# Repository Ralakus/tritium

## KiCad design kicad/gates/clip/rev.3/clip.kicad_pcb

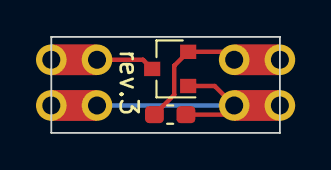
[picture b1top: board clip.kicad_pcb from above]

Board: 2 copper layers, 12.7 x 5.3 mm, 6 parts (0 on the bottom side), 3 nets.

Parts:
J1, J2, J3, J4: Conn_01x01; Hybrid_Castellation_1x01_P2.54
Q1: BSS84; SOT-23
R1: 470k; R_0603_1608Metric_Pad1.05x0.95mm_HandSolder

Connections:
Anode: J1.1, Q1.3
Cathode: J3.1, Q1.2, R1.1
GND: J2.1, J4.1, Q1.1, R1.2

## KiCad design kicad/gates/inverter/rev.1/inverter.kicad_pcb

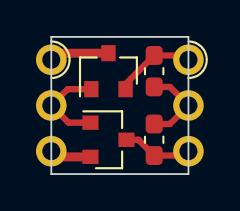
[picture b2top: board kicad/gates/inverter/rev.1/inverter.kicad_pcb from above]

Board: 2 copper layers, 7.6 x 7.6 mm, 6 parts (0 on the bottom side), 6 nets.

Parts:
J1, J2: Conn_01x03; Edge_Castellation_1x03_P2.54
Q1: BSS84; SOT-23
Q2: 2N7002; SOT-23
R1, R2: 12k; R_0603_1608Metric_Pad1.05x0.95mm_HandSolder

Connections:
In: J1.2, Q1.1, Q2.1
Nti: J2.3, Q2.3, R2.2
Out: J2.2, R1.2, R2.1
Pti: J2.1, Q1.2, R1.1
Vdd: J1.1, Q1.3
Vss: J1.3, Q2.2

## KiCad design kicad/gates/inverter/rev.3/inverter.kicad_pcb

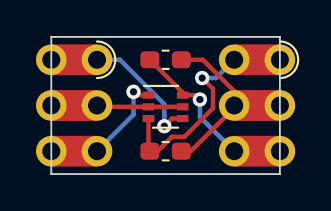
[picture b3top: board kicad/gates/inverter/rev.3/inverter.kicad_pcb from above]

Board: 2 copper layers, 12.7 x 7.6 mm, 5 parts (0 on the bottom side), 6 nets.

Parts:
J1, J2: Conn_01x03; Hybrid_Castellation_1x03_P2.54
Q1: BSS8402DW; SOT-363_SC-70-6
R1, R2: 12k; R_0603_1608Metric_Pad1.05x0.95mm_HandSolder

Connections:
In: J1.2, Q1.2, Q1.5
Nti: J2.3, Q1.6, R2.2
Out: J2.2, R1.2, R2.1
Pti: J2.1, Q1.3, R1.1
Vdd: J1.1, Q1.4
Vss: J1.3, Q1.1

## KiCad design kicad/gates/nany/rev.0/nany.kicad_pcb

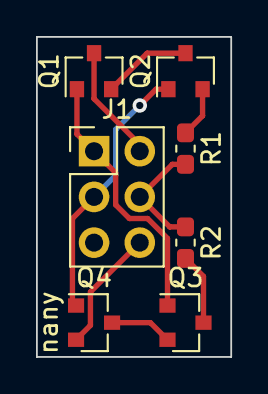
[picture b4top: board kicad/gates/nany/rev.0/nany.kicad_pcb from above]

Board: 2 copper layers, 10.8 x 17.8 mm, 7 parts (0 on the bottom side), 9 nets.

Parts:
J1: Conn_02x03_Odd_Even; PinHeader_2x03_P2.54mm_Vertical
Q1, Q2: BSS84; SOT-23
Q3, Q4: 2N7002; SOT-23
R1, R2: 12k; R_0603_1608Metric_Pad1.05x0.95mm_HandSolder

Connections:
A: J1.1, Q1.1, Q3.1
B: J1.3, Q2.1, Q4.1
unnamed: Q1.2, Q2.3
unnamed: Q2.2, R1.1
unnamed: Q3.2, Q4.3
unnamed: Q3.3, R2.2
Out: J1.4, R1.2, R2.1
Vdd: J1.2, Q1.3
Vss: J1.6, Q4.2

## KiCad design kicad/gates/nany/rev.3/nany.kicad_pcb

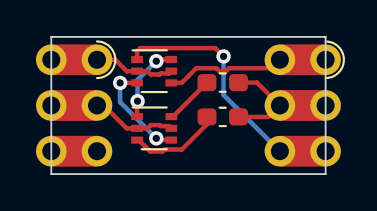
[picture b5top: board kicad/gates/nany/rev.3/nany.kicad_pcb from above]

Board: 2 copper layers, 15.2 x 7.6 mm, 6 parts (0 on the bottom side), 9 nets.

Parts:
J1, J2: Conn_01x03; Hybrid_Castellation_1x03_P2.54
Q1, Q2: BSS8402DW; SOT-363_SC-70-6
R1, R2: 12k; R_0603_1608Metric_Pad1.05x0.95mm_HandSolder

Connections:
A: J1.1, Q1.2, Q1.5
B: J1.2, Q2.2, Q2.5
unnamed: Q1.3, Q2.4
unnamed: Q1.6, Q2.1
unnamed: Q2.3, R1.1
unnamed: Q2.6, R2.2
Out: J2.2, R1.2, R2.1
Vdd: J2.1, Q1.4
Vss: J2.3, Q1.1
